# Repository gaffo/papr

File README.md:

# Gaffo PAPR

PAPR is a *P*owered *A*ir-*P*urifying *R*espirator. It is a hood with a supply that blows filtered air to a worker in a dirty environment. It is much less tiring to wear than masks or other methods.

This is my open documenation on research I have done into a PAPR device which can be hopefully used by others. All of this work is open source. Working on the licensing.

# Structure
This repository is broken up into eletrical, software, and mechanical sections. 

Electrical: Schematics, board layouts, etc for control boards and motors.
Software: Firmware, utilities, etc.
Mechanical: Enclosures, Test Rigs, Etc.

# Licensing

Due to how licensing works the different trees will likely have different licenses. Since everythign in this repo is currently just done by me, I feel free to relicense my work at any time.

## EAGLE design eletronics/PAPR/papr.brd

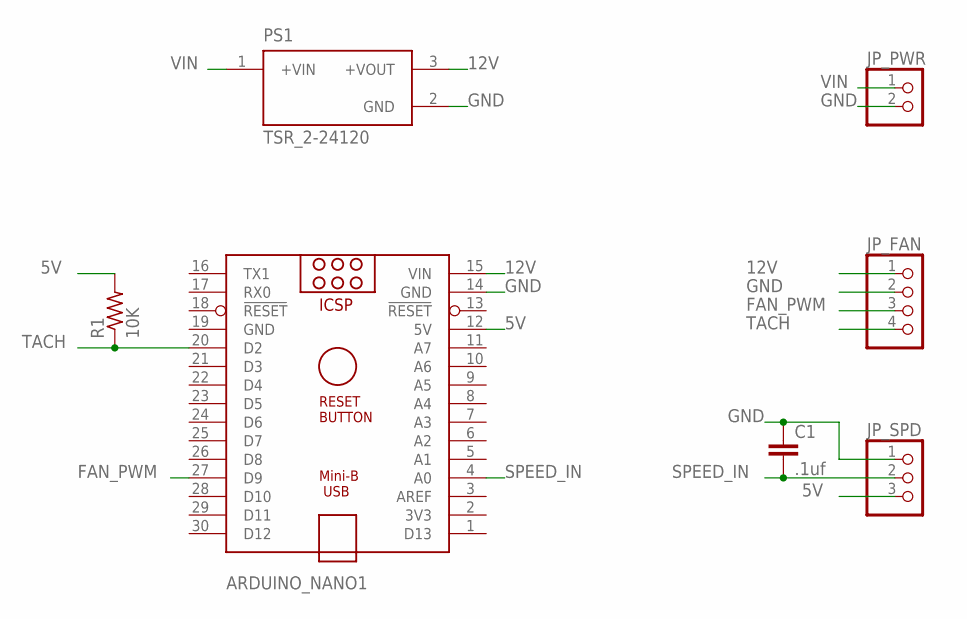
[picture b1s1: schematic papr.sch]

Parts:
ARDUINO_NANO1: ARDUINO_NANO
C1: .1uf; C2.5-3
JP_FAN: PINHD-1X4; 1X04
JP_PWR: PINHD-1X2; 1X02
JP_SPD: PINHD-1X3; 1X03
PS1: TSR_2-24120; CONV_TSR_2-24120
R1: 10K; 0204/5

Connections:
5V: ARDUINO_NANO1.12 (5V), JP_SPD.3, R1.2
12V: ARDUINO_NANO1.15 (VIN), JP_FAN.1, PS1.3 (+VOUT)
FAN_PWM: ARDUINO_NANO1.27 (D9), JP_FAN.3
GND: ARDUINO_NANO1.14 (GND), ARDUINO_NANO1.19 (GND), C1.1, JP_FAN.2, JP_PWR.2, JP_SPD.1, PS1.2 (GND)
SPEED_IN: ARDUINO_NANO1.4 (A0), C1.2, JP_SPD.2
TACH: ARDUINO_NANO1.20 (D2), JP_FAN.4, R1.1
VIN: JP_PWR.1, PS1.1 (+VIN)

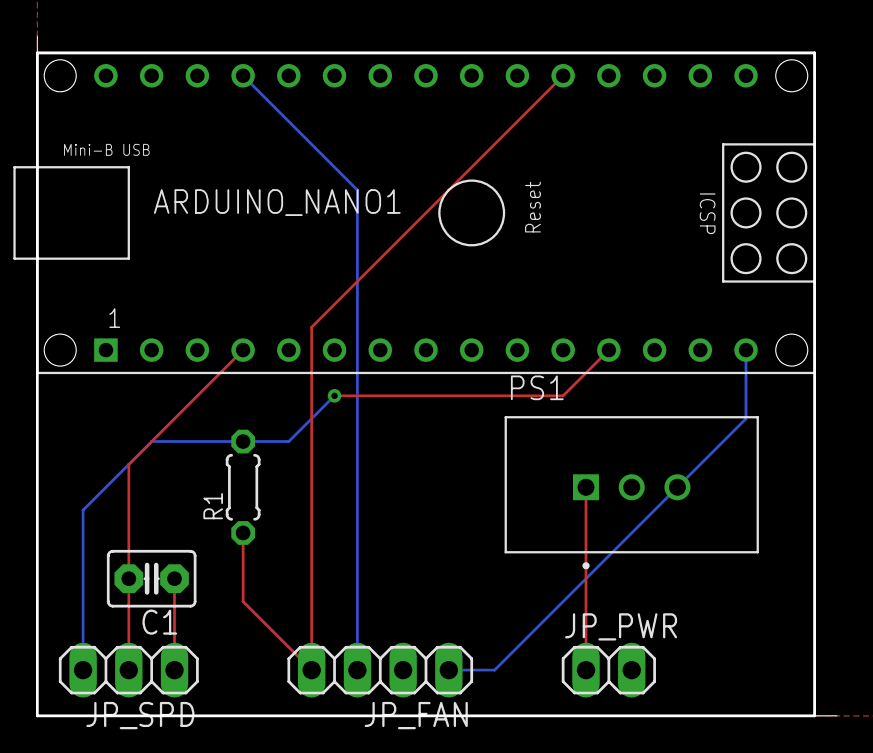
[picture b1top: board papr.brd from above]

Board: 2 copper layers, 44.4 x 37.7 mm, 7 parts (0 on the bottom side), 7 nets.

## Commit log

2020-04-12 Setting up basic repo
2020-04-25 Working up pid control of the fan
2020-04-25 working on rpm feedbac, I think there's a hwardwrae issue
2020-04-25 Reading a pot
2020-04-26 HArdware updates
2020-04-27 Made battery mount and working on basic electronics
2020-04-30 Checkpoint
2020-05-01 Added pullup resistor
2020-05-01 Routed fan pwm solely on the bottom layer, had pointless short top trace
